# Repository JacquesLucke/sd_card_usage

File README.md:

[Schematic](https://jacqueslucke.github.io/sd_card_usage/sd_card_usage_schematic.pdf)

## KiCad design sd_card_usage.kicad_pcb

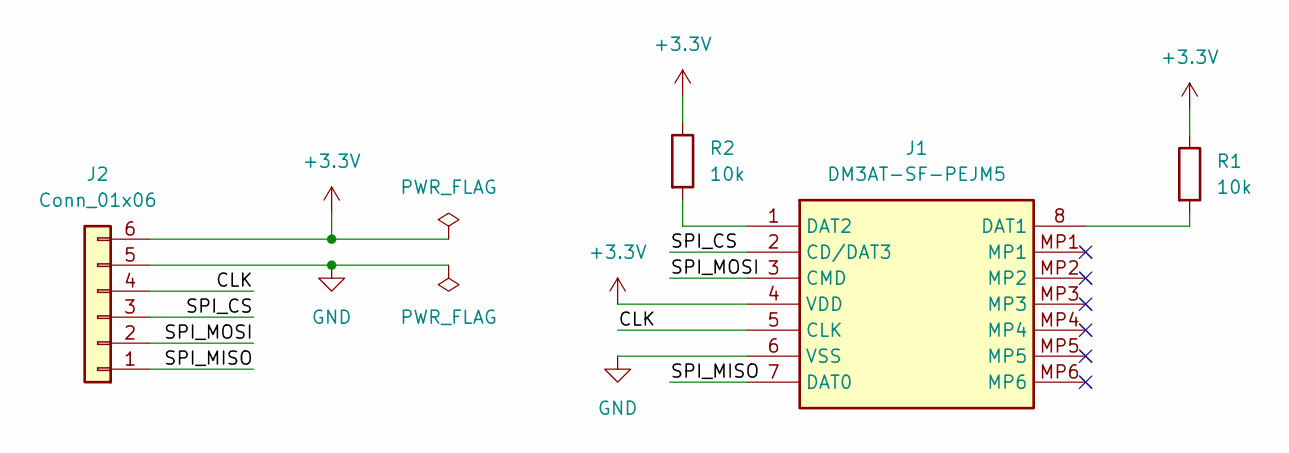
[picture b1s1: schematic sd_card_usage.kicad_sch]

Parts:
J1: DM3AT-SF-PEJM5; DM3ATSFPEJM5; Manufacturer_Part_Number DM3AT-SF-PEJM5; Mouser Part Number 798-DM3AT-SF-PEJM5
J2: Conn_01x06; PinHeader_1x06_P2.54mm_Vertical_SMD_Pin1Left
R1, R2: 10k; R_0603_1608Metric_Pad0.98x0.95mm_HandSolder

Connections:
+3.3V: J1.4 (VDD), J2.6, R1.1, R2.1
/CLK: J1.5 (CLK), J2.4
/SPI_CS: J1.2 (CD/DAT3), J2.3
/SPI_MISO: J1.7 (DAT0), J2.1
/SPI_MOSI: J1.3 (CMD), J2.2
GND: J1.6 (VSS), J2.5
unnamed: J1.8 (DAT1), R1.2
unnamed: J1.1 (DAT2), R2.2

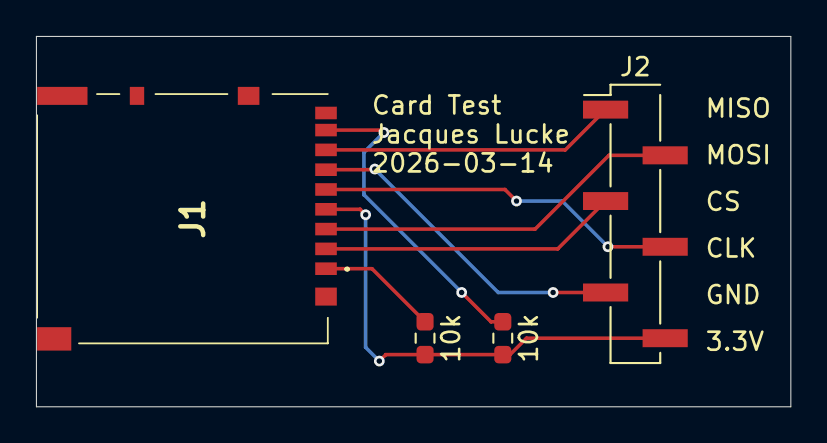
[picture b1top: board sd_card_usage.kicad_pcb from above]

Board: 2 copper layers, 41.9 x 20.6 mm, 4 parts (0 on the bottom side), 8 nets.

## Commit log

2026-03-14 configure kibot
2026-03-14 add 3d model
2026-03-14 update path
